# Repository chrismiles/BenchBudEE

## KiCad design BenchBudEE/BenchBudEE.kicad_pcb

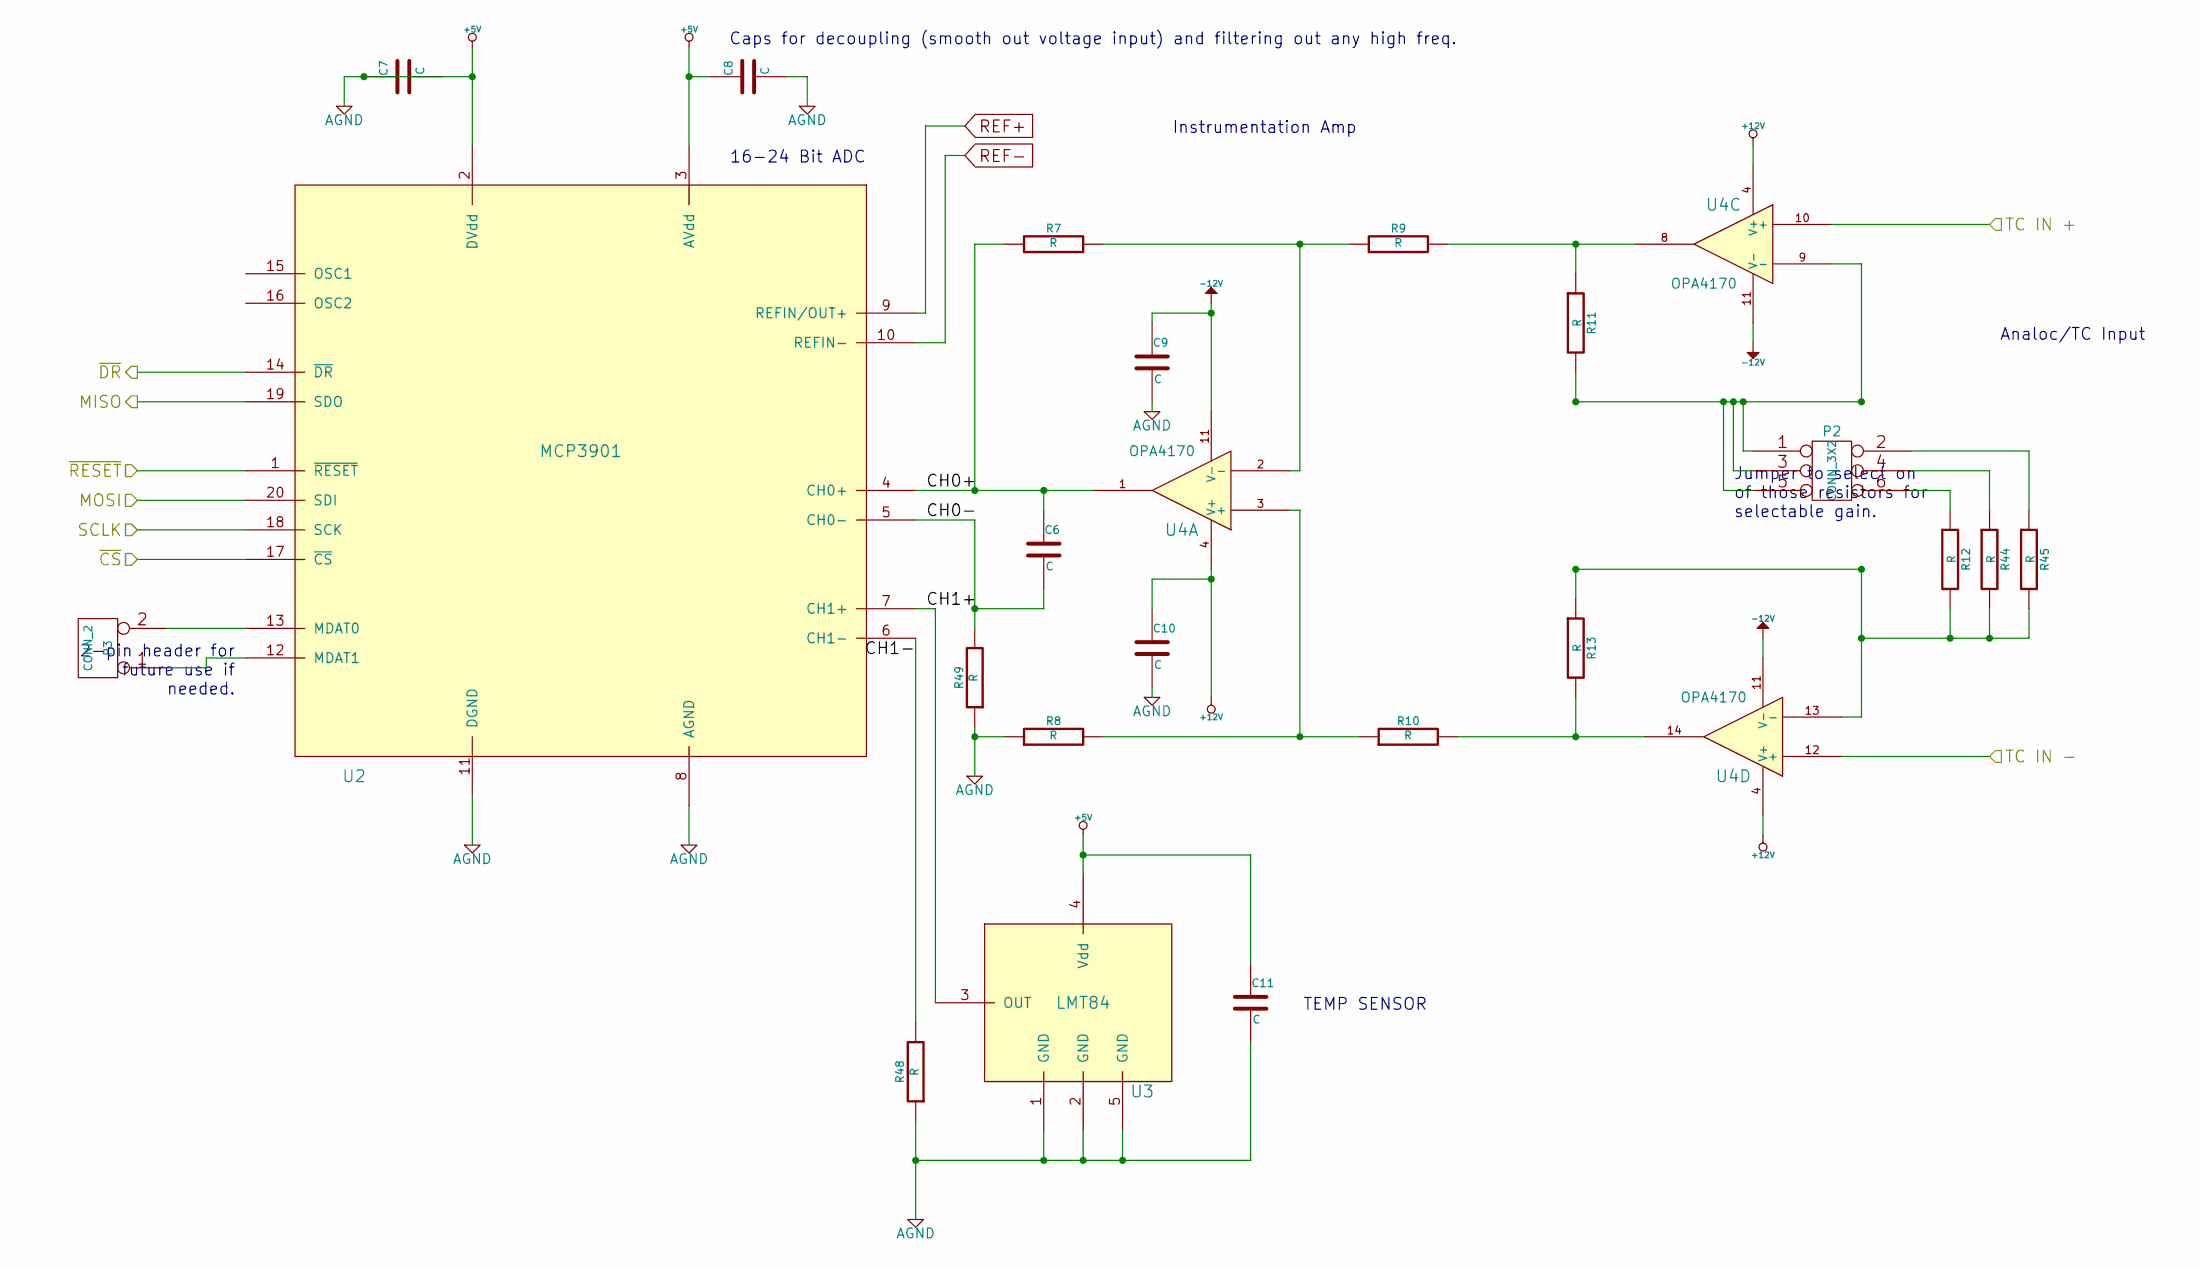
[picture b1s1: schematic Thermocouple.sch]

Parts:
C6, C7, C8, C9, C10, C11: C
P2: CONN_3X2
P3: CONN_2
R7, R8, R9, R10, R11, R12, R13, R44, R45, R48, R49: R
U2: MCP3901
U3: LMT84
U4: OPA4170

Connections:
+5V: C7.1, C8.1, C8.2, C9.2, C10.2, C11.1, C11.2, R8.1, R48.1, R49.1, U2.2 (DVdd), U2.3 (AVdd), U2.8 (AGND), U2.11 (DGND), U3.1 (GND), U3.2 (GND), U3.4 (Vdd), U3.5 (GND); also elsewhere on the board
+12V: C10.1, U4.4 (V+); also elsewhere on the board
-12V: C9.1, U4.11 (V-); also elsewhere on the board
/Arduino/MISO: U2.19 (SDO); also elsewhere on the board
/Arduino/MOSI: U2.20 (SDI); also elsewhere on the board
/Arduino/SCLK: U2.18 (SCK); also elsewhere on the board
/Arduino/~ADC_CS: U2.17 (~CS); also elsewhere on the board
/Arduino/~DR: U2.14 (~DR); also elsewhere on the board
/Arduino/~RESET: U2.1 (~RESET); also elsewhere on the board
/Thermocouple/CH0+: C6.1, R7.1, U2.4 (CH0+), U4.1
/Thermocouple/CH0-: C6.2, R49.2, U2.5 (CH0-)
/Thermocouple/CH1+: U2.7 (CH1+), U3.3 (OUT)
/Thermocouple/CH1-: R48.2, U2.6 (CH1-)
/Thermocouple/TC IN +: U4.10 (+); also elsewhere on the board
/Thermocouple/TC IN -: U4.12 (+); also elsewhere on the board
unnamed: P3.1, U2.12 (MDAT1)
unnamed: P3.2 (PM), U2.13 (MDAT0)
unnamed: P2.6, R12.1
unnamed: P2.4, R44.1
unnamed: P2.2, R45.1
unnamed: R7.2, R9.1, U4.2 (-)
unnamed: R8.2, R10.1, U4.3 (+)
unnamed: R9.2, R11.1, U4.8
unnamed: R10.2, R13.2, U4.14
unnamed: P2.1, P2.3, P2.5, R11.2, U4.9 (-)
unnamed: R12.2, R13.1, R44.2, R45.2, U4.13 (-)

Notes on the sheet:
Analoc/TC Input
Instrumentation Amp
Jumper to select on of those resistors for selectable gain.
Caps for decoupling (smooth out voltage input) and filtering out any high freq.
TEMP SENSOR
16-24 Bit ADC
2-pin header for future use if needed.

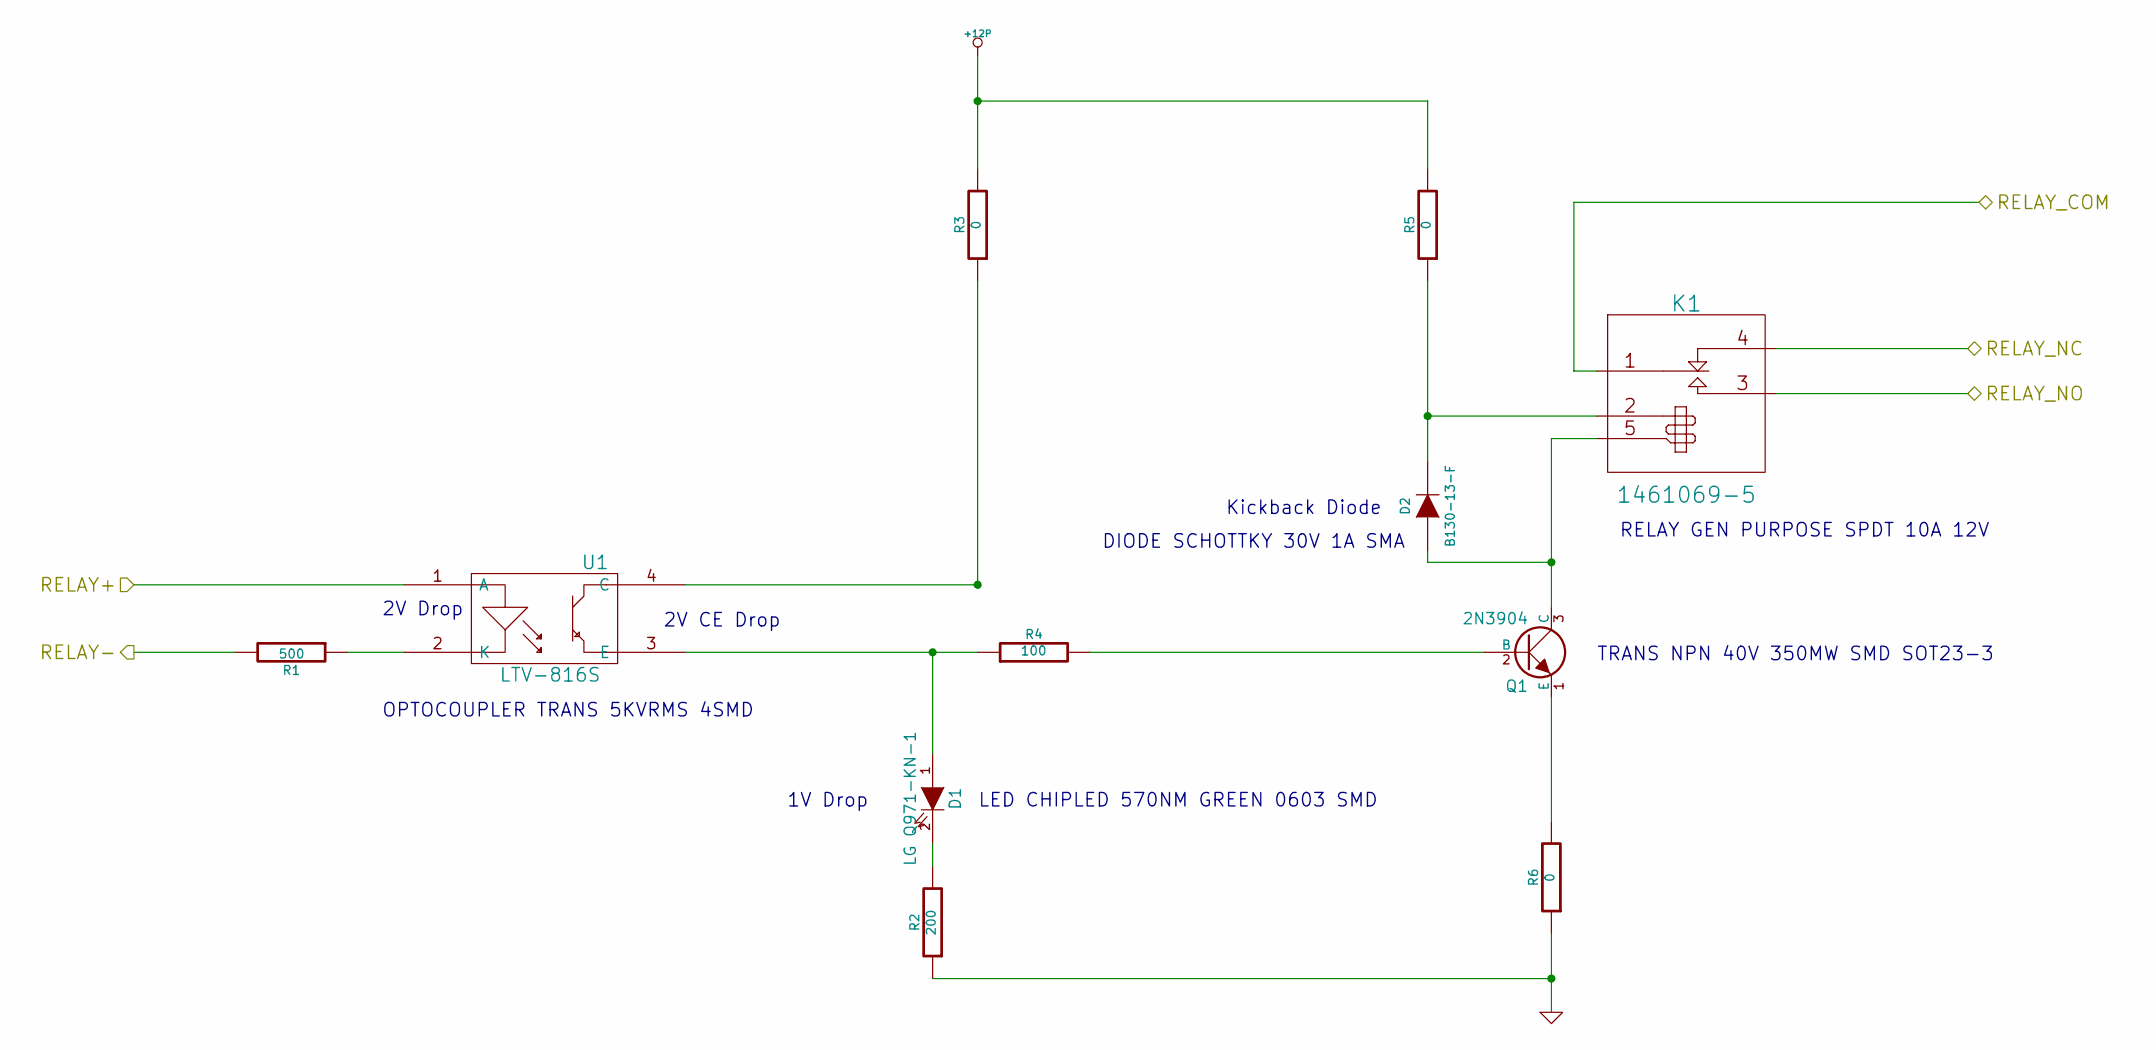
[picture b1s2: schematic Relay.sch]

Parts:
D1: LG Q971-KN-1
D2: B130-13-F
K1: 1461069-5
Q1: 2N3904; MFG Part Number MMBT3904-7-F
R1: 500
R2: 200
R3, R5, R6: 0
R4: 100
U1: LTV-816S; MFG Part Number LTV-816S

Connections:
+12P: R3.2, R5.2; also elsewhere on the board
/Arduino/RELAY+: U1.1 (A); also elsewhere on the board
/Arduino/RELAY-: R1.2; also elsewhere on the board
/Relay/RELAY_COM: K1.1 (COM); also elsewhere on the board
/Relay/RELAY_NC: K1.4 (NC); also elsewhere on the board
/Relay/RELAY_NO: K1.3 (NO); also elsewhere on the board
GND: R2.1, R6.1; also elsewhere on the board
unnamed: D1.2 (K), R2.2
unnamed: R1.1, U1.2 (K)
unnamed: D1.1 (A), R4.1, U1.3 (E)
unnamed: Q1.1 (E), R6.2
unnamed: Q1.2 (B), R4.2
unnamed: D2.2 (K), K1.2 (COIL+), R5.1
unnamed: R3.1, U1.4 (C)
unnamed: D2.1 (A), K1.5 (COIL-), Q1.3 (C)

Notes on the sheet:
Kickback Diode
LED CHIPLED 570NM GREEN 0603 SMD
DIODE SCHOTTKY 30V 1A SMA
OPTOCOUPLER TRANS 5KVRMS 4SMD
TRANS NPN 40V 350MW SMD SOT23-3
RELAY GEN PURPOSE SPDT 10A 12V
2V CE Drop
1V Drop
2V Drop

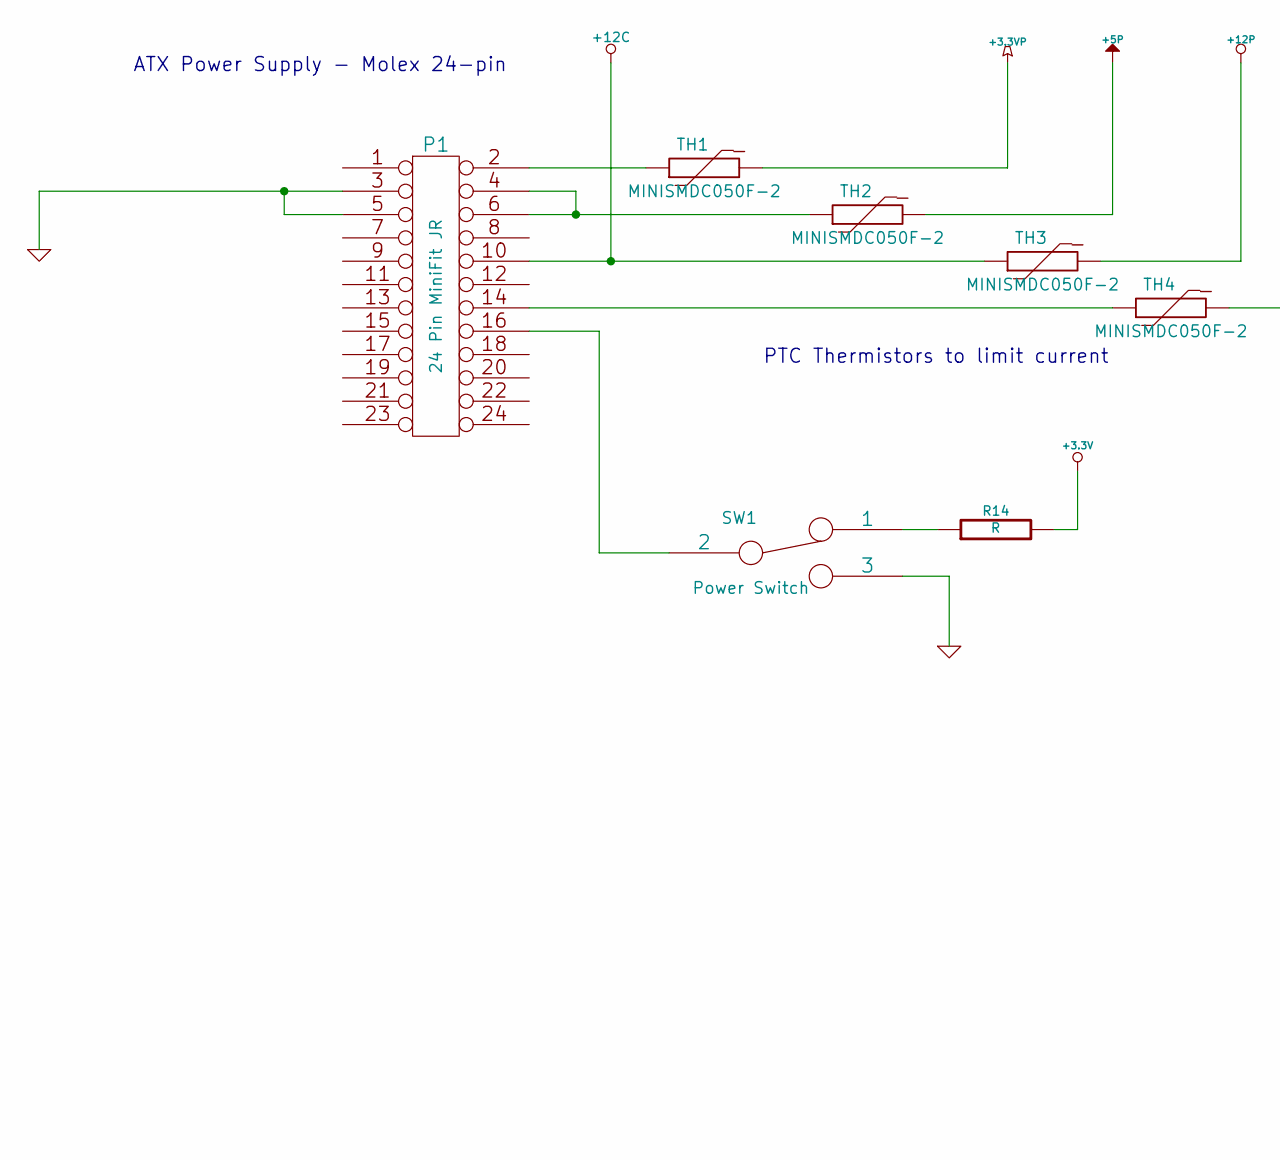
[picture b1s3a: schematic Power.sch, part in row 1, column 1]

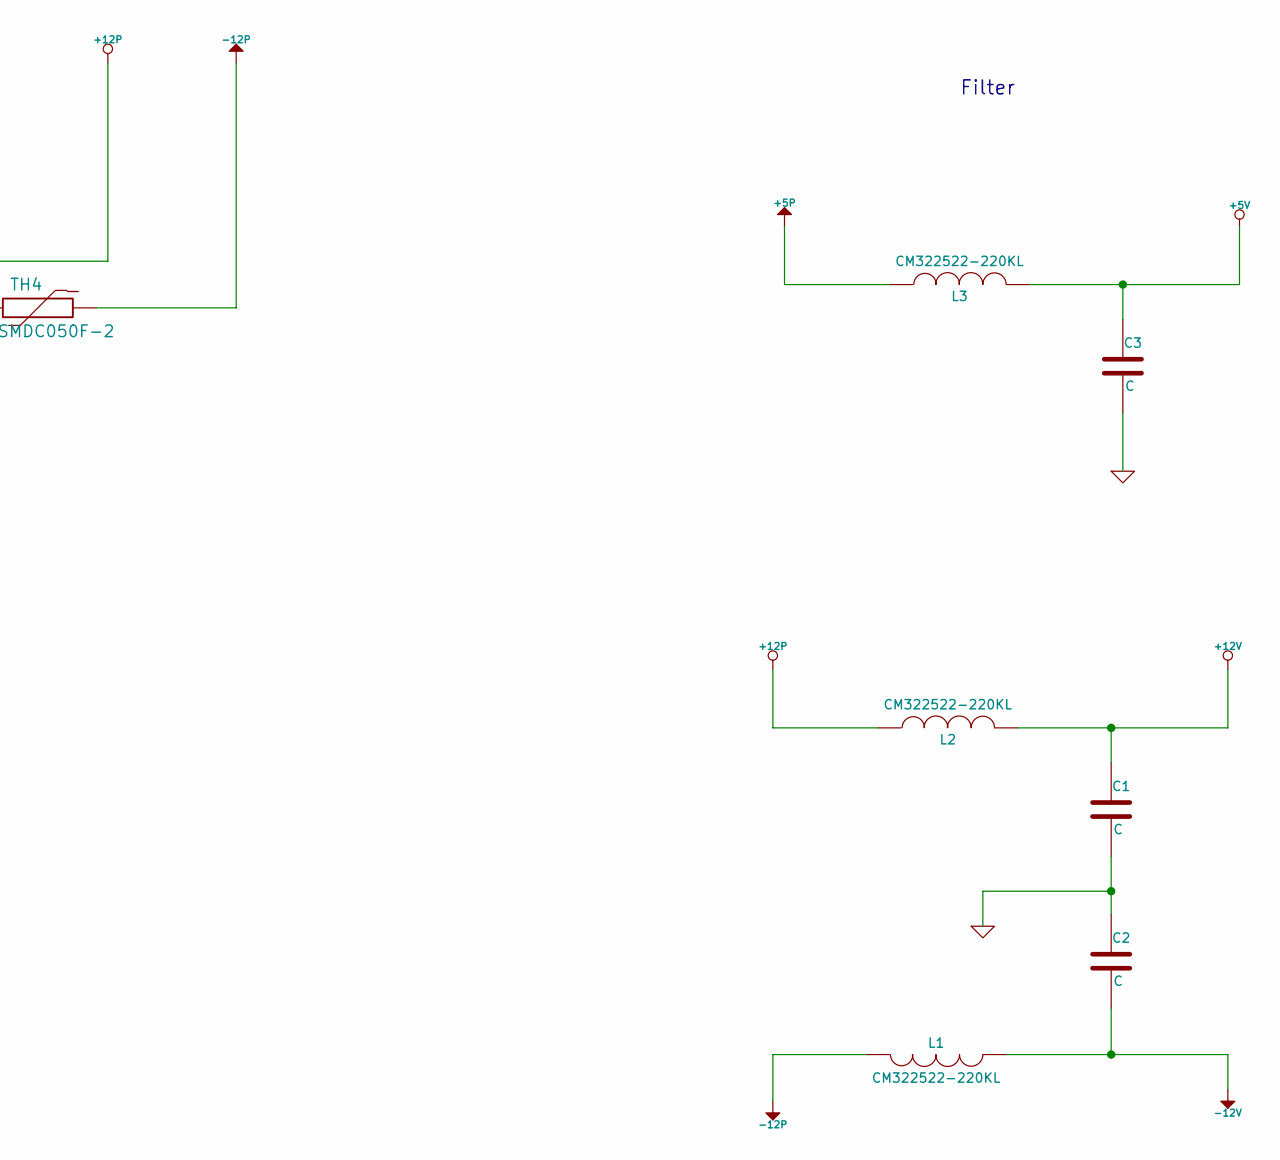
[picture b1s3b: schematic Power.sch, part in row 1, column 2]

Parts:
C1, C2, C3: C
L1, L2, L3: CM322522-220KL; MFG Part Number CM322522-220KL
P1: 24 Pin MiniFit JR; MFG Part Number 39-30-1240
R14: R
SW1: Power Switch; MFG Part Number OS102011MA1QN1
TH1, TH2, TH3, TH4: MINISMDC050F-2; MFG Part Number MINISMDC050F-2

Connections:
+3.3V: R14.2; also elsewhere on the board
+5P: L3.1, TH2.2
+5V: C3.1, L3.2; also elsewhere on the board
+12C: P1.10, TH3.1; also elsewhere on the board
+12P: L2.1, TH3.2; also elsewhere on the board
+12V: C1.1, L2.2; also elsewhere on the board
-12P: L1.1, TH4.2
-12V: C2.2, L1.2; also elsewhere on the board
GND: C1.2, C2.1, C3.2, P1.3, P1.5, SW1.3; also elsewhere on the board
unnamed: P1.14, TH4.1
unnamed: R14.1, SW1.1
unnamed: P1.2, TH1.1
unnamed: P1.16, SW1.2
unnamed: P1.4, P1.6, TH2.1

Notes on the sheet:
ATX Power Supply - Molex 24-pin
Filter
PTC Thermistors to limit current

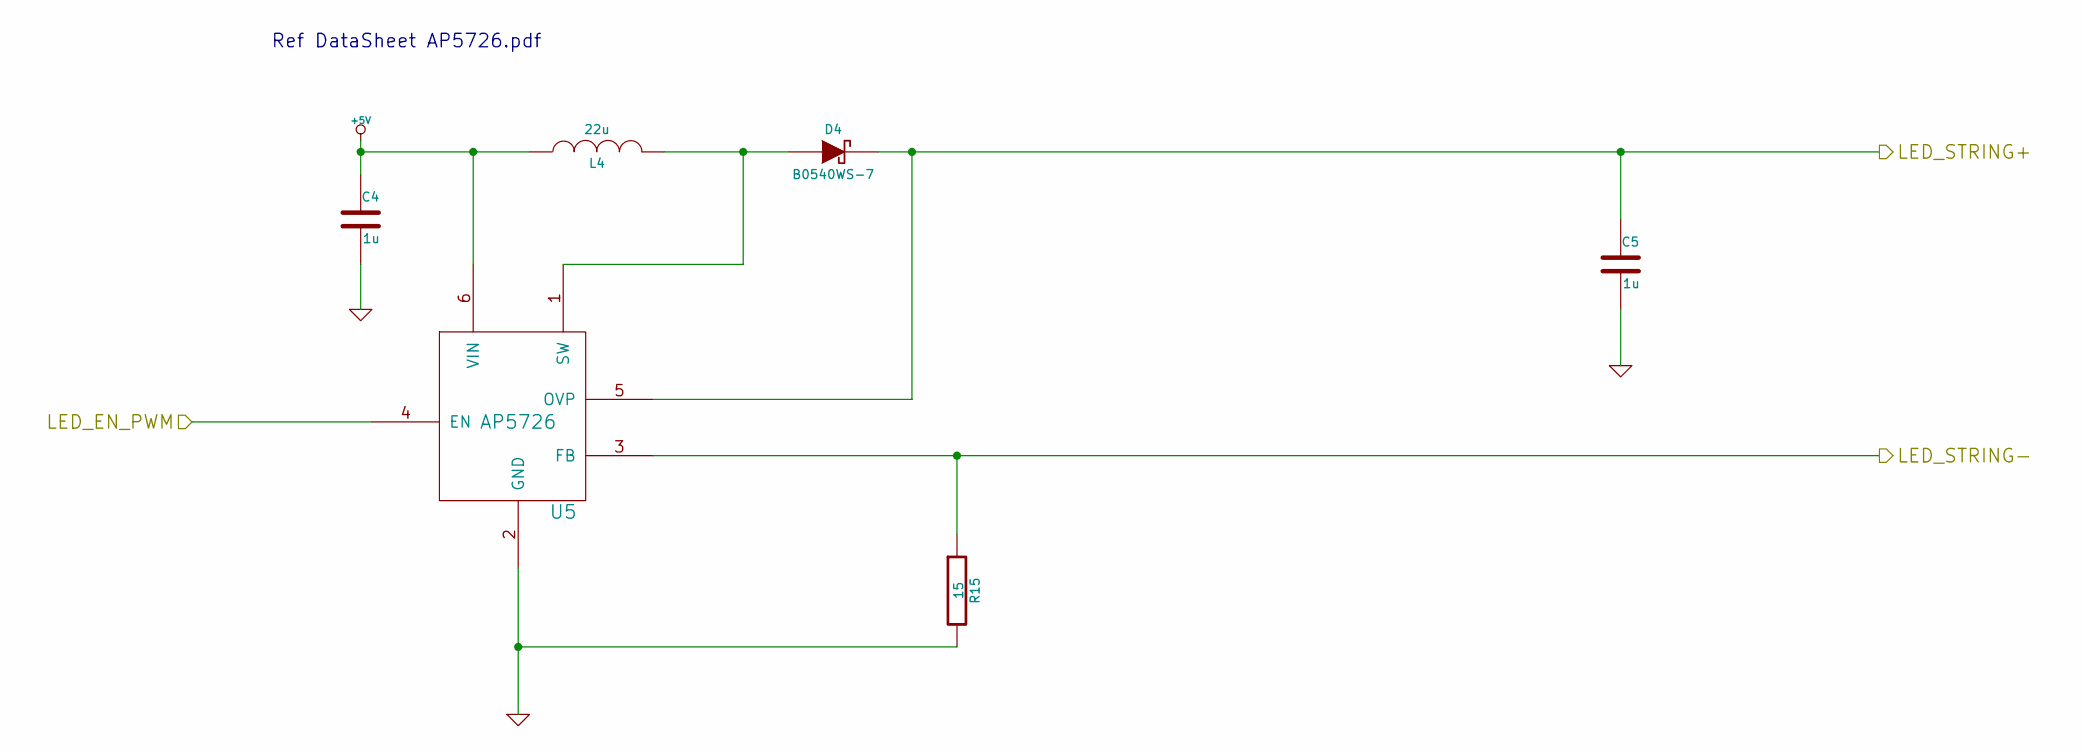
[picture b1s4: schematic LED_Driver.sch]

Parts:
C4, C5: 1u
D4: B0540WS-7; MFG Part Number B0540WS-7
L4: 22u; MFG Part Number NR4012T220M
R15: 15
U5: AP5726; MFG Part Number AP5726WG-7

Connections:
+5V: C4.1, L4.1, U5.6 (VIN); also elsewhere on the board
/Arduino/LED_EN_PWM: U5.4 (EN); also elsewhere on the board
/LED_Driver/LED_STRING+: C5.1, D4.2 (K), U5.5 (OVP); also elsewhere on the board
/LED_Driver/LED_STRING-: R15.1, U5.3 (FB); also elsewhere on the board
GND: C4.2, C5.2, R15.2, U5.2 (GND); also elsewhere on the board
unnamed: D4.1 (A), L4.2, U5.1 (SW)

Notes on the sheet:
Ref DataSheet AP5726.pdf

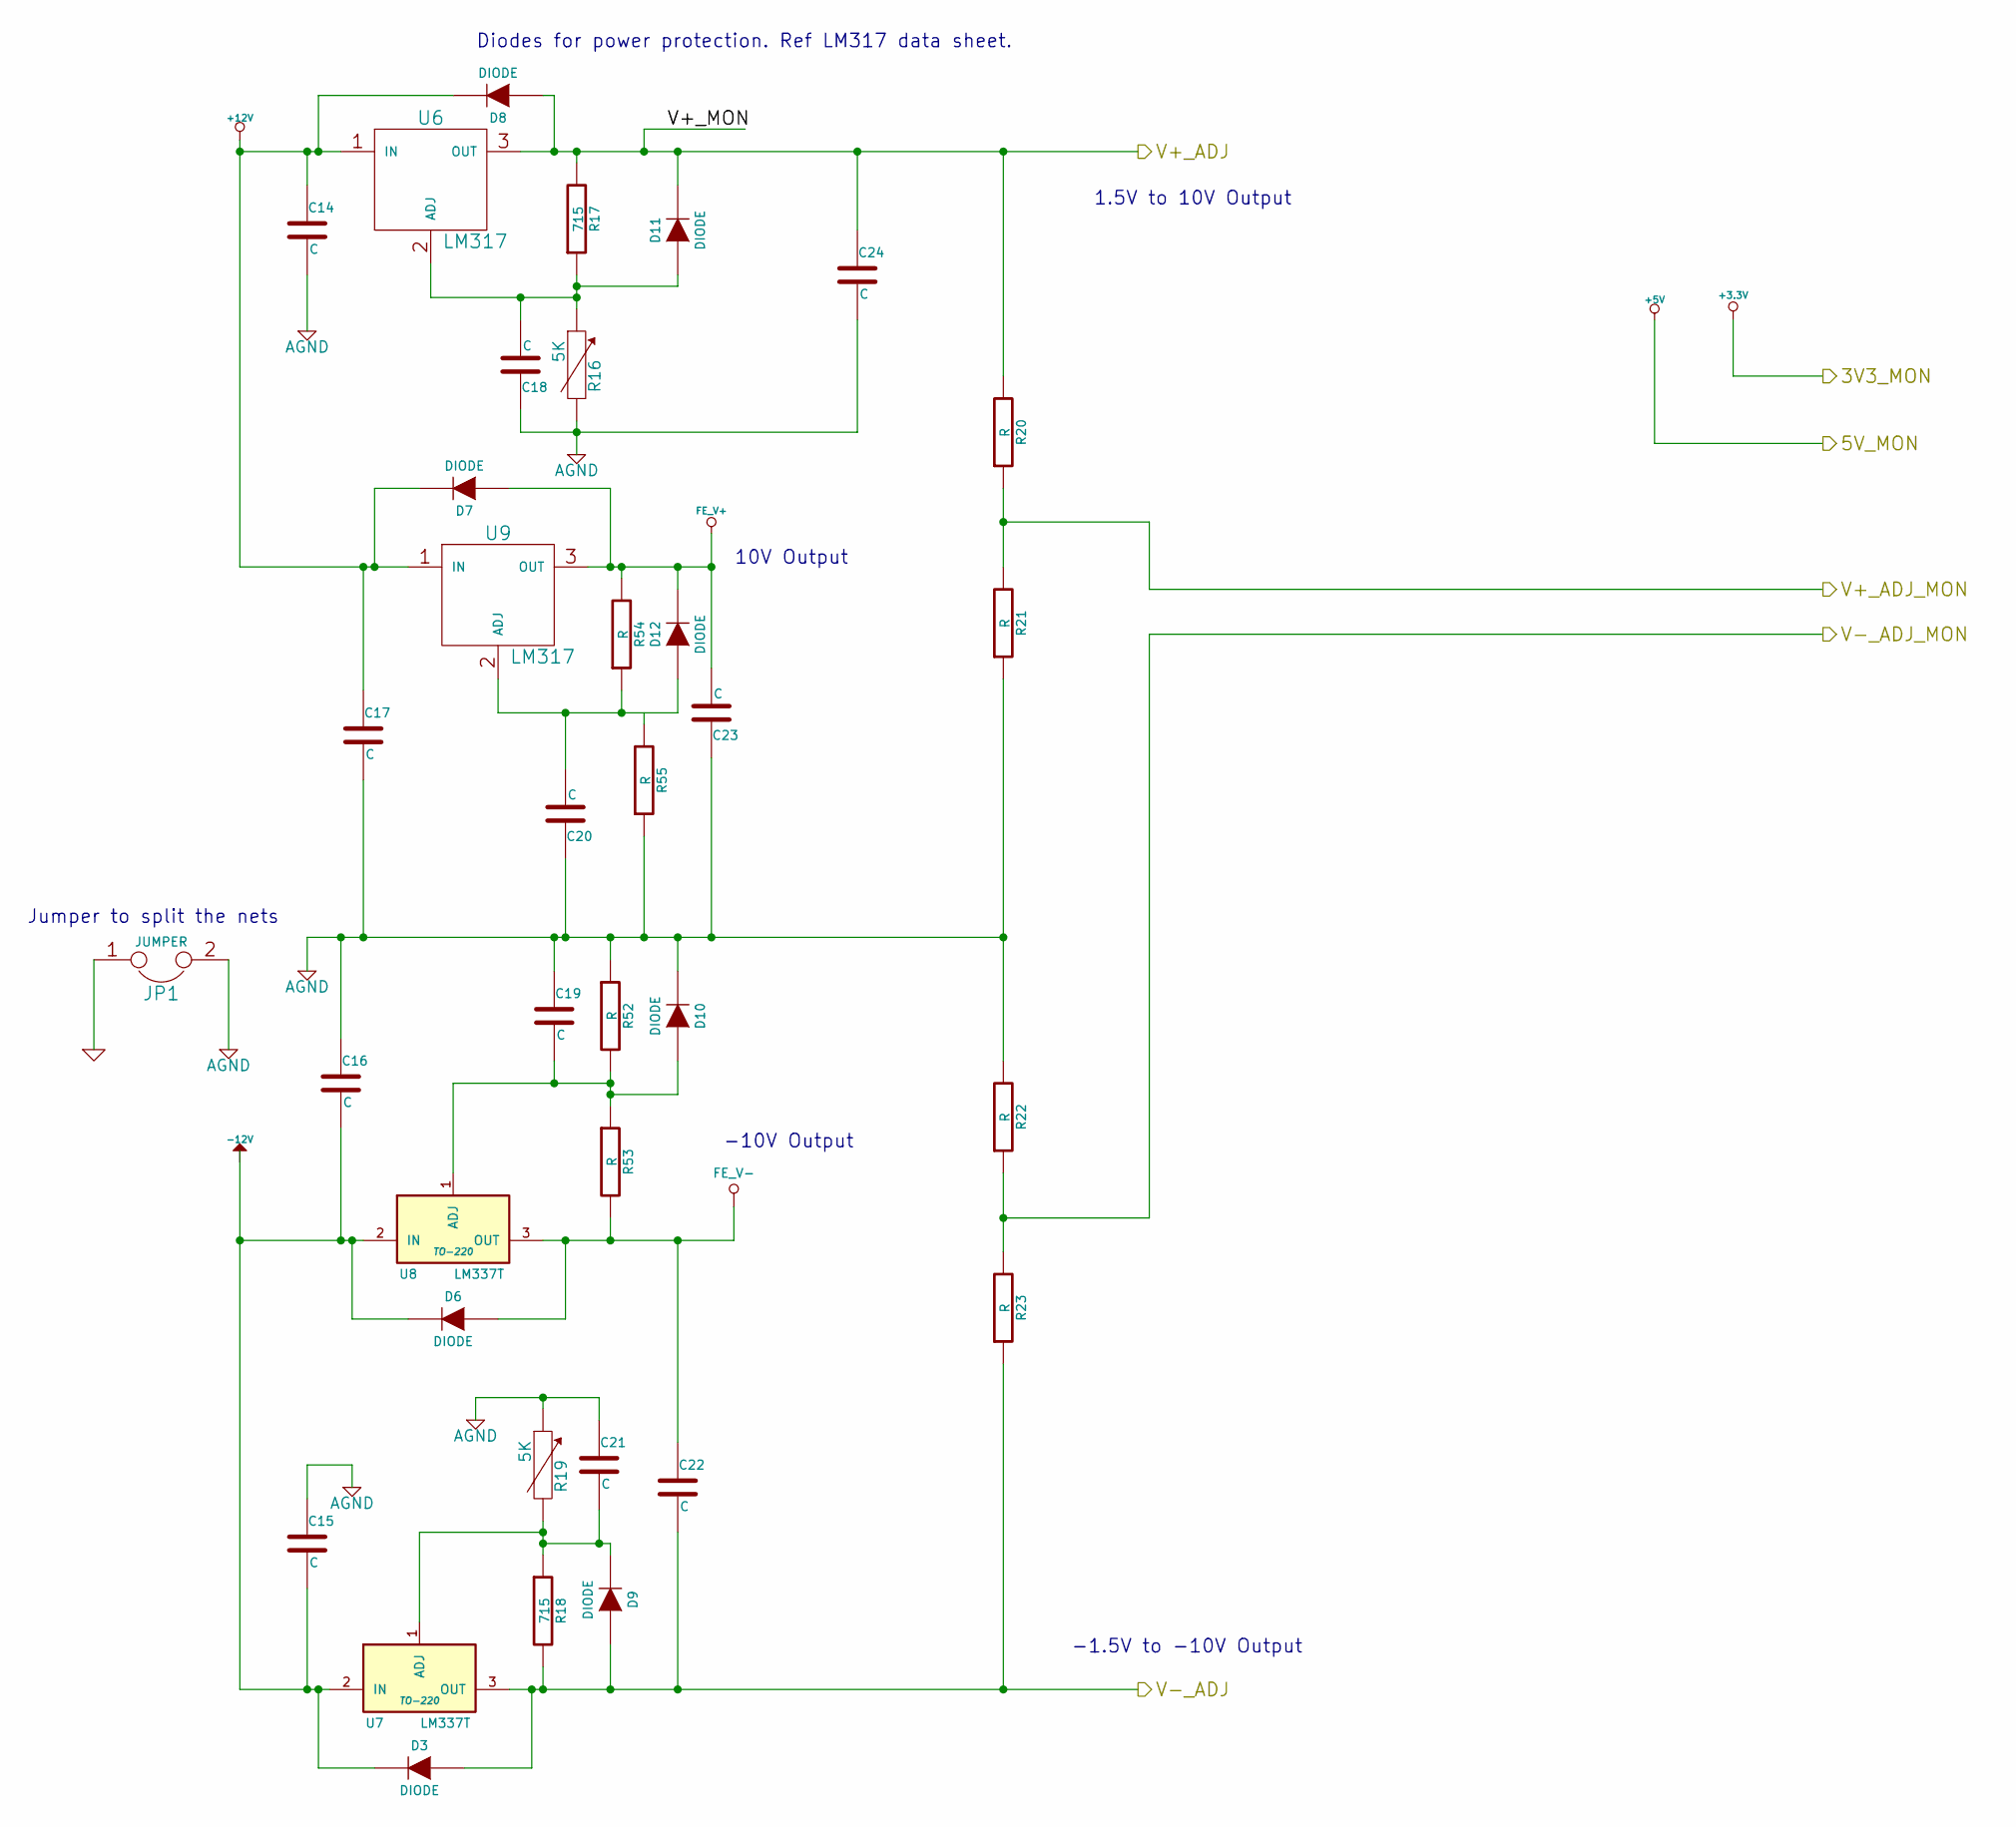
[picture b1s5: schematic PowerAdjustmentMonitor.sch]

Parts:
C14, C15, C16, C17, C18, C19, C20, C21, C22, C23, C24: C
D3, D6, D7, D8, D9, D10, D11, D12: DIODE
JP1: JUMPER
R16, R19: 5K
R17, R18: 715
R20, R21, R22, R23, R52, R53, R54, R55: R
U6, U9: LM317
U7, U8: LM337T; TO-220

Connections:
+5V: C14.2, C15.1, C16.1, C17.2, C18.1, C19.1, C20.1, C21.1, C23.1, C24.2, D10.2 (K), JP1.2, R16.2, R19.1, R21.1, R22.2, R52.1, R55.1; also elsewhere on the board
+12V: C14.1, C17.1, D7.2 (K), D8.2 (K), U6.1 (IN), U9.1 (IN); also elsewhere on the board
/Arduino/V+_ADJ_MON: R20.1, R21.2; also elsewhere on the board
/Arduino/V-_ADJ_MON: R22.1, R23.2; also elsewhere on the board
/PowerAdjustmentMonitor/V+_ADJ: C24.1, D8.1 (A), D11.2 (K), R17.2, R20.2, U6.3 (OUT); also elsewhere on the board
/PowerAdjustmentMonitor/V-_ADJ: C22.2, D3.1 (A), D9.1 (A), R18.2, R23.1, U7.3 (OUT); also elsewhere on the board
FE_V+: C23.2, D7.1 (A), D12.2 (K), R54.2, U9.3 (OUT)
FE_V-: C22.1, D6.1 (A), R53.2, U8.3 (OUT)
unnamed: C21.2, D9.2 (K), R18.1, R19.2, U7.1 (ADJ)
unnamed: C15.2, C16.2, D3.2 (K), D6.2 (K), U7.2 (IN), U8.2 (IN)
unnamed: C19.2, D10.1 (A), R52.2, R53.1, U8.1 (ADJ)
unnamed: C20.2, D12.1 (A), R54.1, U9.2 (ADJ)
unnamed: C18.2, D11.1 (A), R16.1, R17.1, U6.2 (ADJ)

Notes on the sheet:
Jumper to split the nets
10V Output
1.5V to 10V Output
-10V Output
-1.5V to -10V Output
Diodes for power protection. Ref LM317 data sheet.

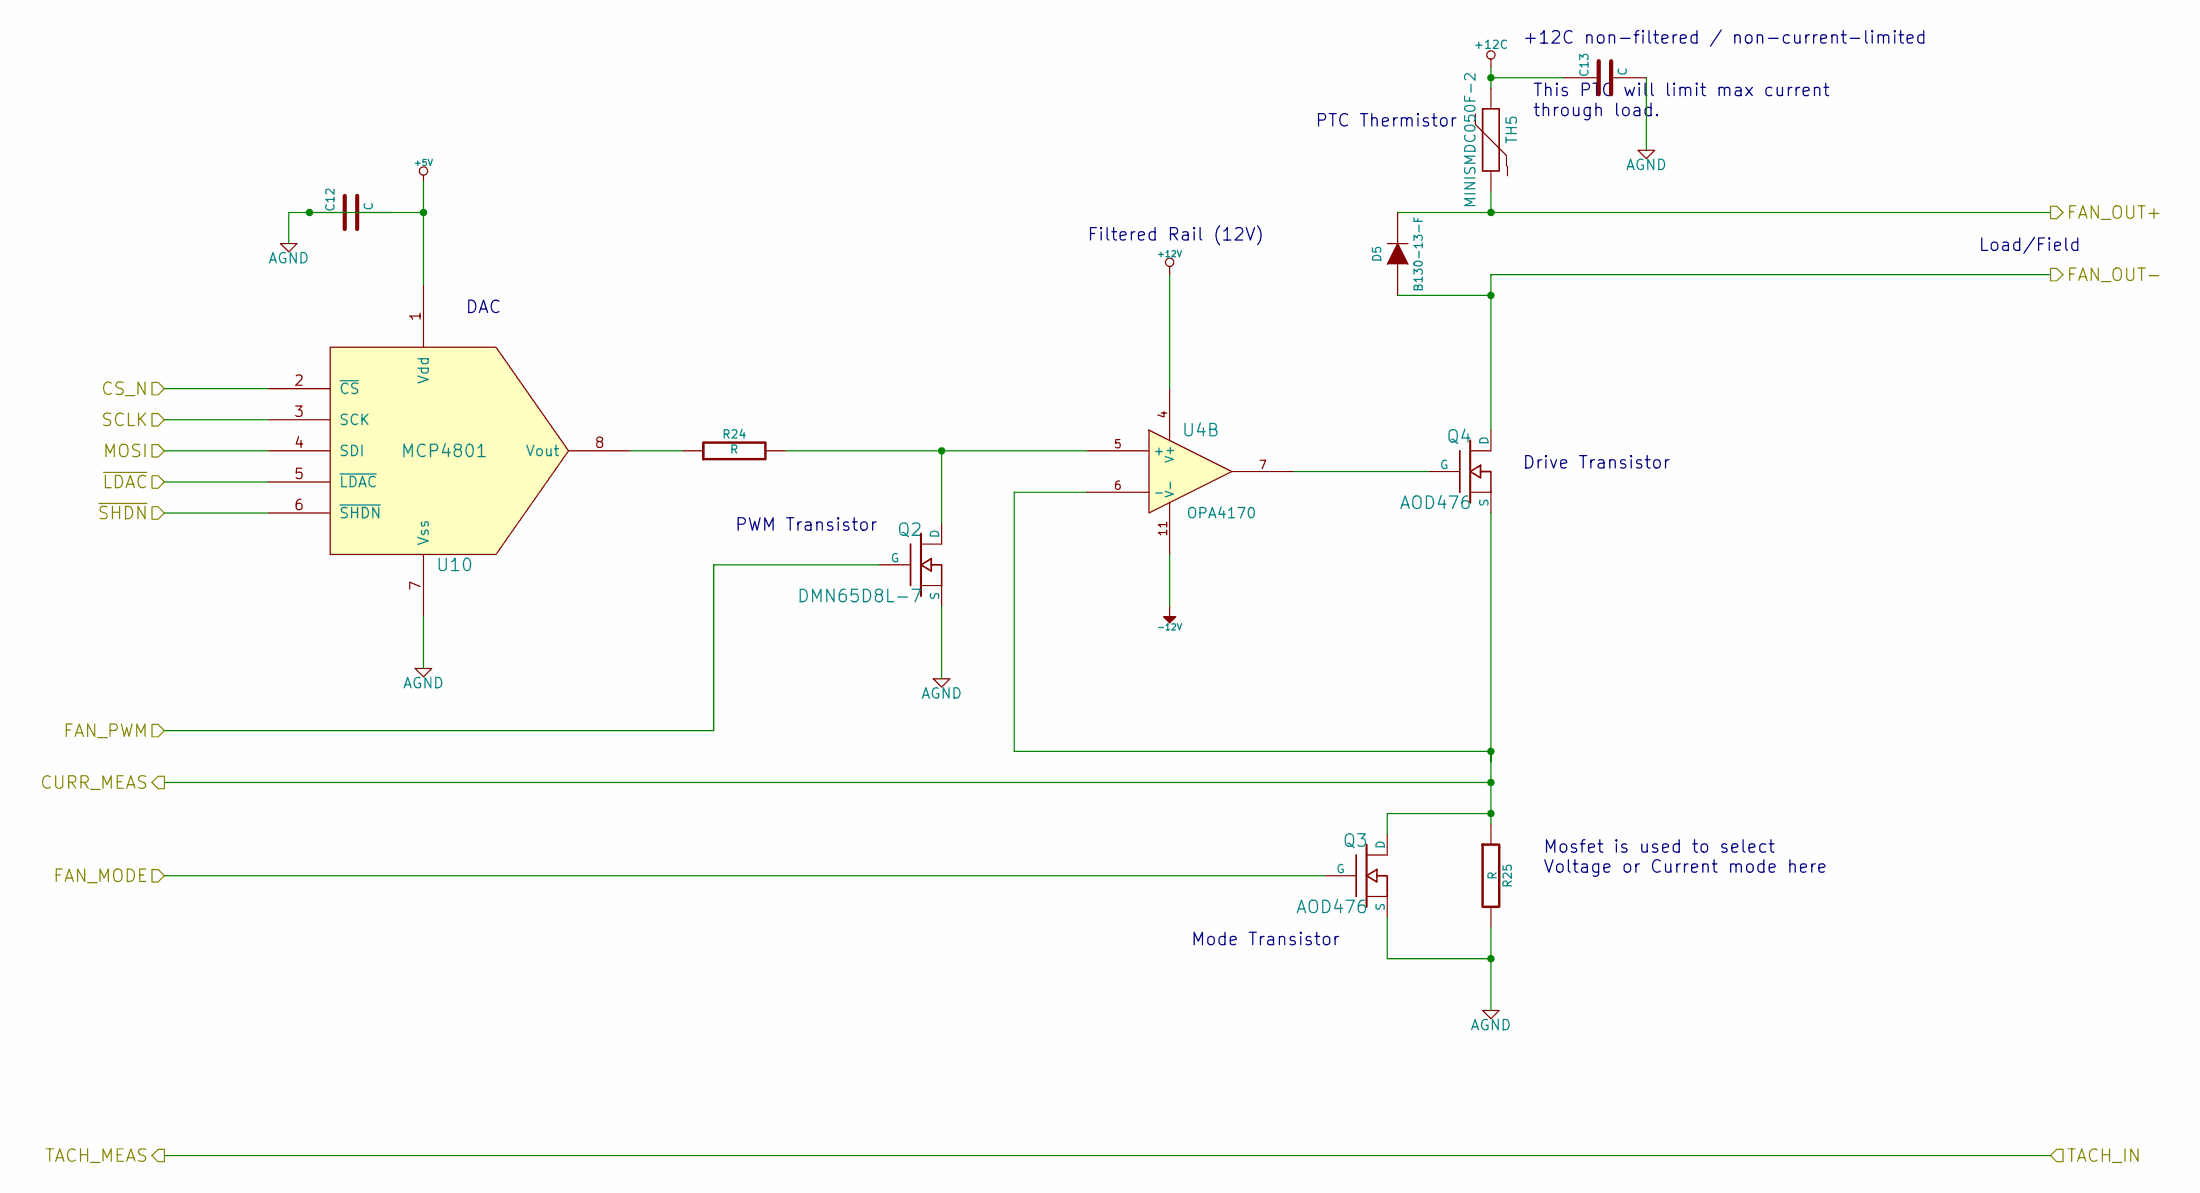
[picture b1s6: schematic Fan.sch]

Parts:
C12, C13: C
D5: B130-13-F; MFG Part Number B130-13-F
Q2: DMN65D8L-7; MFG Part Number DMN65D8L-7
Q3, Q4: AOD476; MFG Part Number AOD476
R24, R25: R
TH5: MINISMDC050F-2; MFG Part Number MINISMDC050F-2
U4: OPA4170
U10: MCP4801

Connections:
+5V: C12.1, C13.2, Q2.3 (S), Q2.S, Q3.3 (S), R25.2, U10.1 (Vdd), U10.7 (Vss); also elsewhere on the board
+12C: C13.1, TH5.1; also elsewhere on the board
+12V: U4.4 (V+); also elsewhere on the board
-12V: U4.11 (V-); also elsewhere on the board
/Arduino/CURR_MEAS: Q3.2 (D), Q4.3 (S), R25.1, U4.6 (-); also elsewhere on the board
/Arduino/FAN_MODE: Q3.1 (G); also elsewhere on the board
/Arduino/FAN_PWM: Q2.G; also elsewhere on the board
/Arduino/MOSI: U10.4 (SDI); also elsewhere on the board
/Arduino/SCLK: U10.3 (SCK); also elsewhere on the board
/Arduino/~LDAC: U10.5 (~LDAC); also elsewhere on the board
/Arduino/~SHDN: U10.6 (~SHDN); also elsewhere on the board
/Fan/CS_N: U10.2 (~CS); also elsewhere on the board
/Fan/FAN_OUT+: D5.2 (K), TH5.2; also elsewhere on the board
/Fan/FAN_OUT-: D5.1 (A), Q4.2 (D); also elsewhere on the board
unnamed: R24.1, U10.8 (Vout)
unnamed: Q2.2 (D), Q2.D, R24.2, U4.5 (+)
unnamed: Q4.1 (G), U4.7

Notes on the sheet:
DAC
Filtered Rail (12V)
This PTC will limit max current through load.
Load/Field
Mosfet is used to select Voltage or Current mode here
+12C non-filtered / non-current-limited
Drive Transistor
PWM Transistor
Mode Transistor
PTC Thermistor

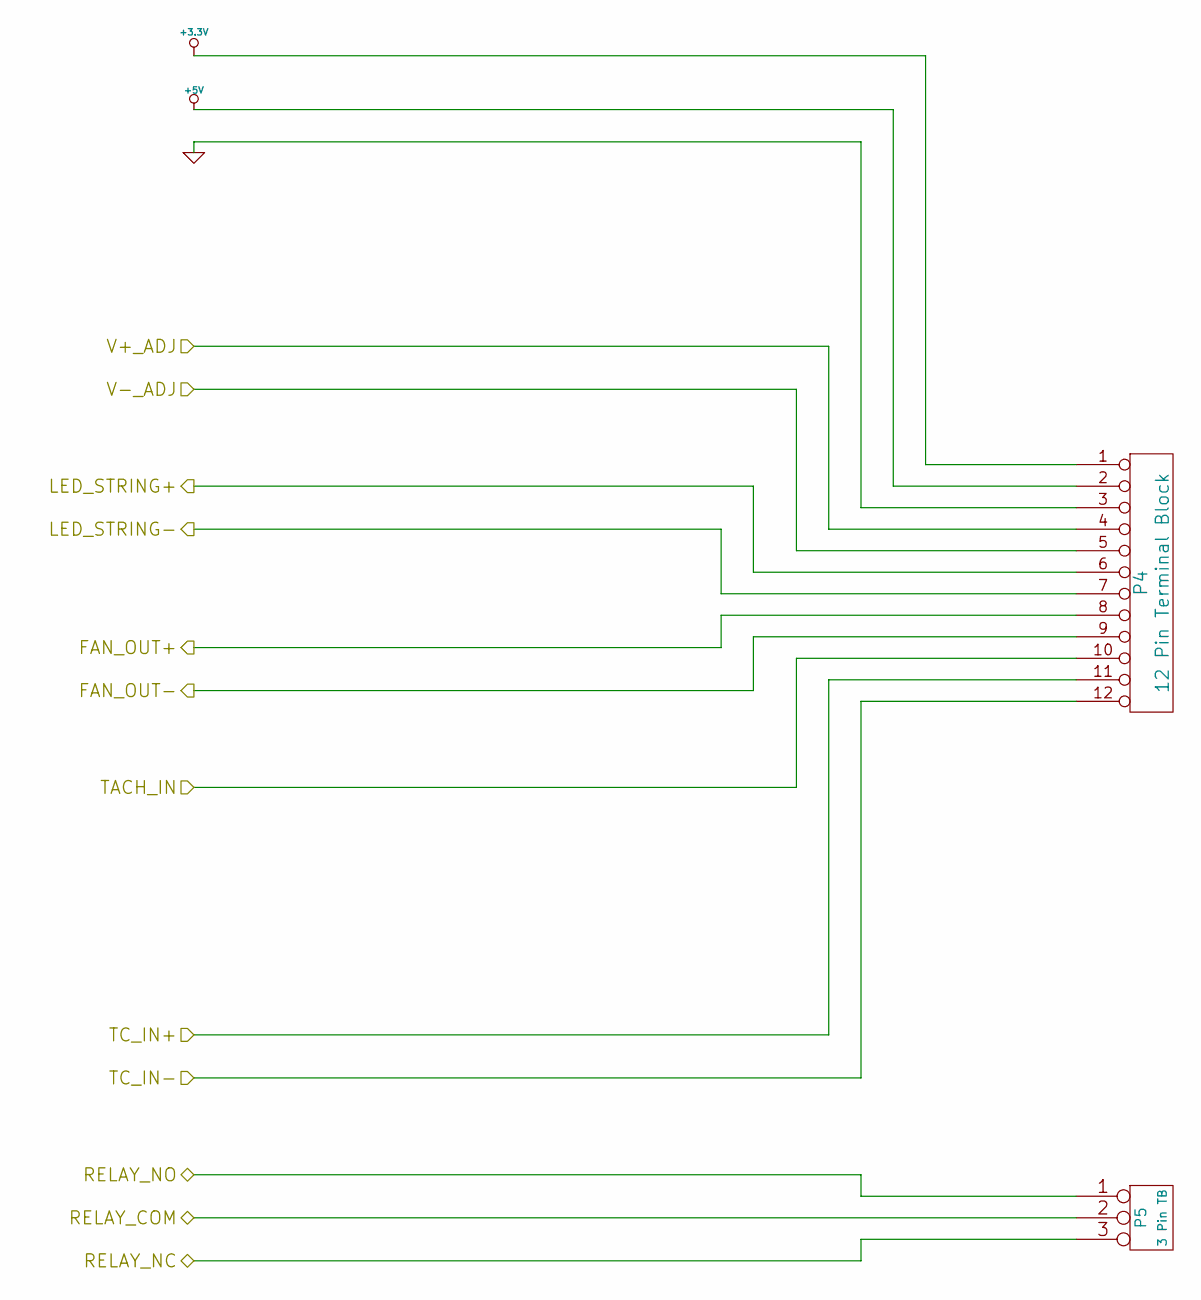
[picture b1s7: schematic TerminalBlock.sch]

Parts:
P4: 12 Pin Terminal Block; MFG Part Number OSTTE120104
P5: 3 Pin TB; MFG Part Number 1935174

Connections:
+3.3V: P4.1; also elsewhere on the board
+5V: P4.2; also elsewhere on the board
/Fan/FAN_OUT+: P4.8; also elsewhere on the board
/Fan/FAN_OUT-: P4.9; also elsewhere on the board
/Fan/TACH_IN: P4.10; also elsewhere on the board
/LED_Driver/LED_STRING+: P4.6; also elsewhere on the board
/LED_Driver/LED_STRING-: P4.7; also elsewhere on the board
/PowerAdjustmentMonitor/V+_ADJ: P4.4; also elsewhere on the board
/PowerAdjustmentMonitor/V-_ADJ: P4.5; also elsewhere on the board
/Relay/RELAY_COM: P5.2 (PM); also elsewhere on the board
/Relay/RELAY_NC: P5.3; also elsewhere on the board
/Relay/RELAY_NO: P5.1; also elsewhere on the board
/Thermocouple/TC IN +: P4.11; also elsewhere on the board
/Thermocouple/TC IN -: P4.12; also elsewhere on the board
GND: P4.3; also elsewhere on the board
